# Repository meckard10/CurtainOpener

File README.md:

# CurtainOpener

*Continuation of 4820_AlarmClock project.*
*Melody Eckard, Elliot Phillips, Madeline Woehrman*

Melody Eckard

## Overview

Light-sensitive window curtain opener that will automatically open user's curtains to 
allow natural light to wake them up. UtilizesMSP430 to sense outside light and control 
the cutain opener.

## Folders

1. /schematics
	- contains pcb schematic files and 3D print designs

2. /code
	- contains MSP430 code files

3. /original\ material/
	- contains imported files from original project

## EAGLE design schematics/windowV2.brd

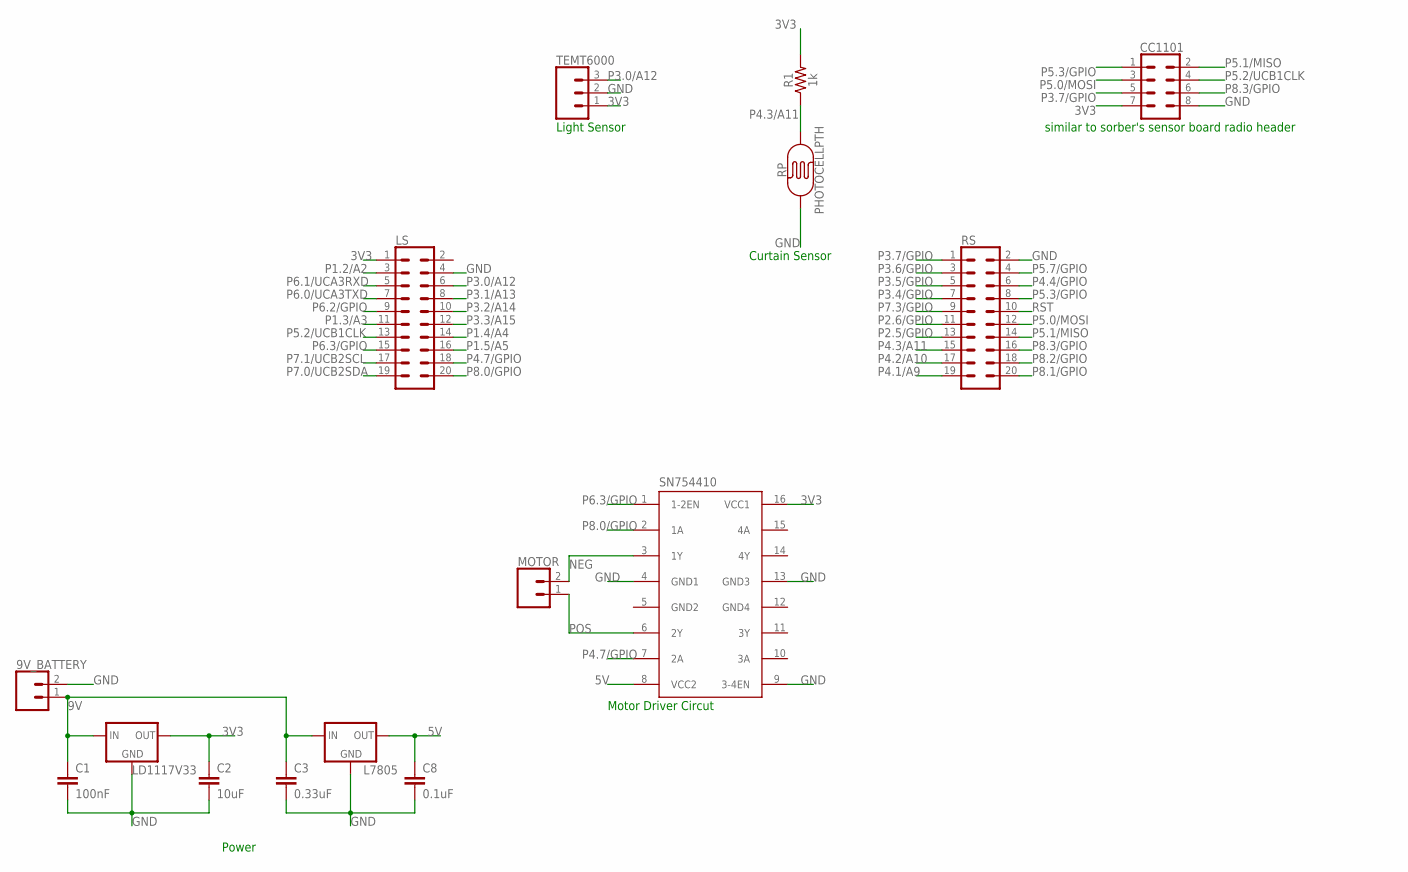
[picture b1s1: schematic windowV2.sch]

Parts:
9V_BATTERY: CONN_02; 1X02
C1: 100nF; C2.5-2
C2: 10uF; C2.5-2
C3: 0.33uF; C2.5-2
C8: 0.1uF; C2.5-2
CC1101: CONN_04X2; 2X4
L7805: V_REG_78XX-TO-220; TO-220-ALT
LD1117V33: V_REG_LD1117VXX; TO-220-ALT2
LS: CONN_10X2; 2X10
MOTOR: CONN_02; 1X02
R1: 1k; AXIAL-0.3
RP: PHOTOCELLPTH; PHOTOCELL
RS: CONN_10X2; 2X10
SN754410: L293D; DIL16
TEMT6000: 455-1750-1-ND; 1X03

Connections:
3V3: C2.1, CC1101.7, LD1117V33.OUT, LS.1, R1.P$2 (2), SN754410.16 (VCC1), TEMT6000.1
5V: C8.1, L7805.OUT, SN754410.8 (VCC2)
9V: 9V_BATTERY.1, C1.1, C3.1, L7805.IN, LD1117V33.IN
GND: 9V_BATTERY.2, C1.2, C2.2, C3.2, C8.2, CC1101.8, L7805.GND, LD1117V33.GND, LS.4, RP.1, RS.2, SN754410.4 (GND1), SN754410.9 (3-4EN), SN754410.13 (GND3), TEMT6000.2
GND2: SN754410.5 (GND2)
GND4: SN754410.12 (GND4)
NEG: MOTOR.2, SN754410.3 (1Y)
P1.2/A2: LS.3
P1.3/A3: LS.11
P1.4/A4: LS.14
P1.5/A5: LS.16
P2.5/GPIO: RS.13
P2.6/GPIO: RS.11
P3.0/A12: LS.6, TEMT6000.3
P3.1/A13: LS.8
P3.2/A14: LS.10
P3.3/A15: LS.12
P3.4/GPIO: RS.7
P3.5/GPIO: RS.5
P3.6/GPIO: RS.3
P3.7/GPIO: CC1101.5, RS.1
P4.1/A9: RS.19
P4.2/A10: RS.17
P4.3/A11: R1.P$1 (1), RP.2, RS.15
P4.4/GPIO: RS.6
P4.7/GPIO: LS.18, SN754410.7 (2A)
P5.0/MOSI: CC1101.3, RS.12
P5.1/MISO: CC1101.2, RS.14
P5.2/UCB1CLK: CC1101.4, LS.13
P5.3/GPIO: CC1101.1, RS.8
P5.7/GPIO: RS.4
P6.0/UCA3TXD: LS.7
P6.1/UCA3RXD: LS.5
P6.2/GPIO: LS.9
P6.3/GPIO: LS.15, SN754410.1 (1-2EN)
P7.0/UCB2SDA: LS.19
P7.1/UCB2SCL: LS.17
P7.3/GPIO: RS.9
P8.0/GPIO: LS.20, SN754410.2 (1A)
P8.1/GPIO: RS.20
P8.2/GPIO: RS.18
P8.3/GPIO: CC1101.6, RS.16
POS: MOTOR.1, SN754410.6 (2Y)
RST: RS.10

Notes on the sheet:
similar to sorber's sensor board radio header
Light Sensor
Motor Driver Circut
Power
Curtain Sensor

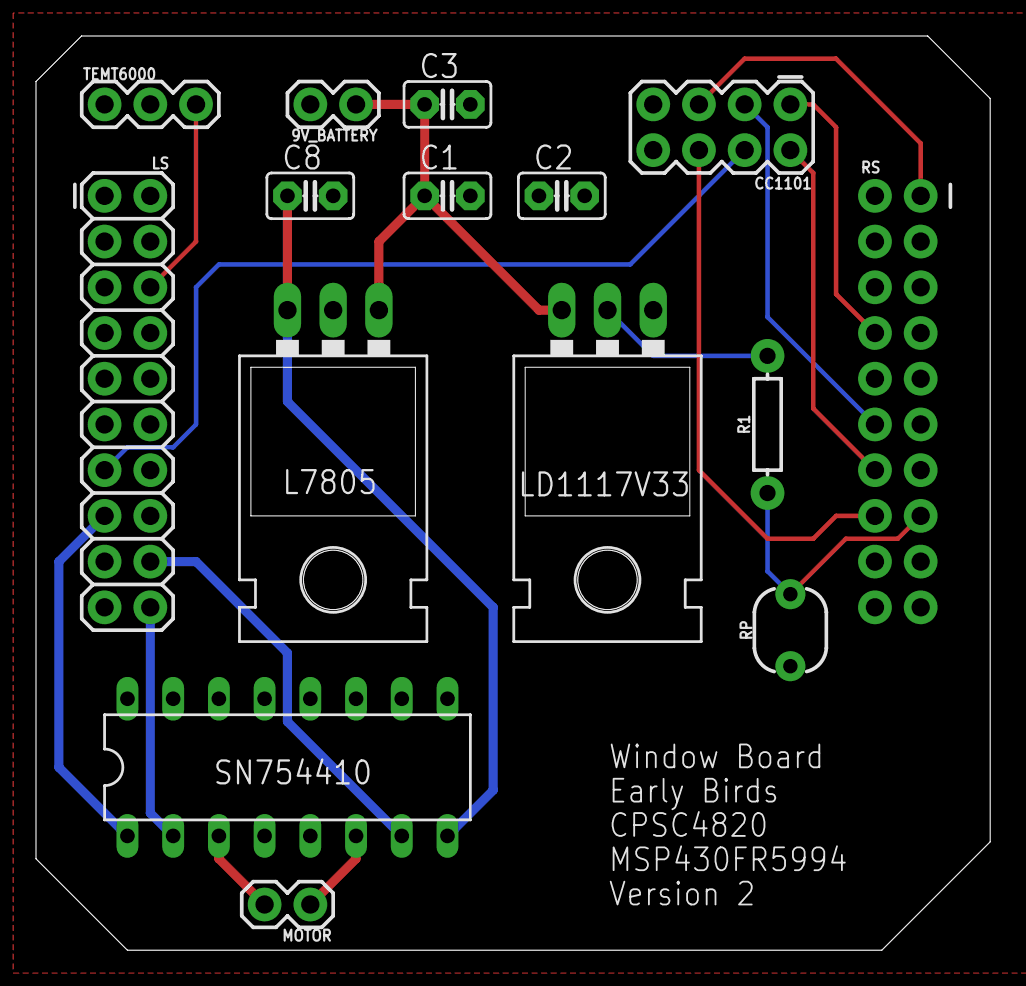
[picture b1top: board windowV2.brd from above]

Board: 2 copper layers, 53.0 x 50.8 mm, 15 parts (1 on the bottom side), 17 nets.

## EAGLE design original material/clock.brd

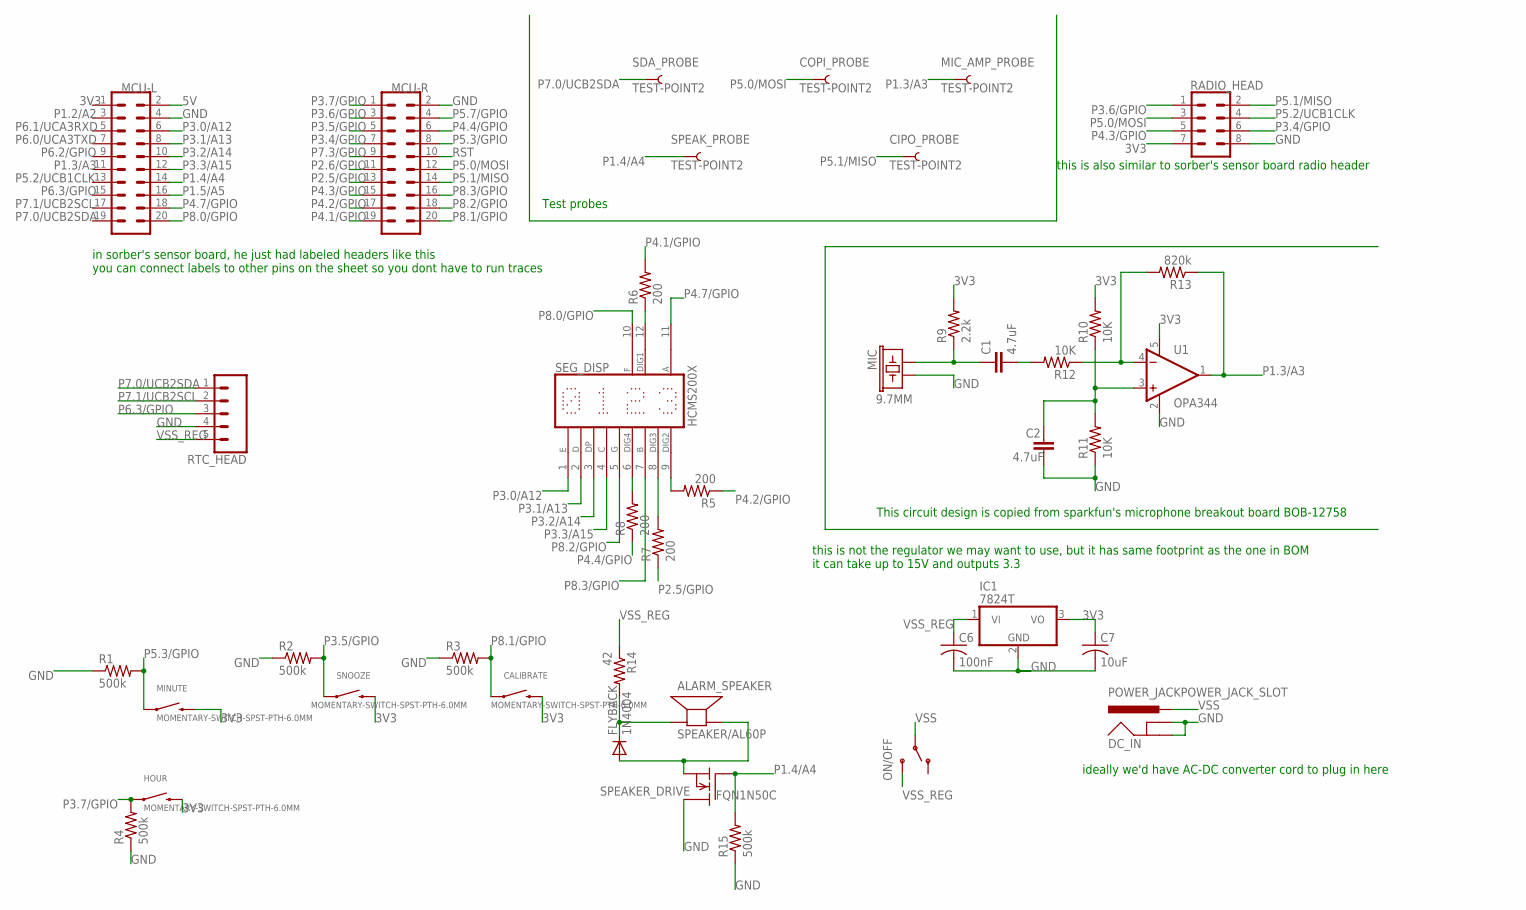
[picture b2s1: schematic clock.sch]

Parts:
ALARM_SPEAKER: SPEAKER/AL60P; AL60P
C1, C2: 4.7uF; 0603-CAP
C6: 100nF; C0805
C7: 10uF; C0805
CALIBRATE: MOMENTARY-SWITCH-SPST-PTH-6.0MM; TACTILE_SWITCH_PTH_6.0MM
CIPO_PROBE: TEST-POINT2; PAD.02X.02
COPI_PROBE: TEST-POINT2; PAD.02X.02
DC_IN: POWER_JACKPOWER_JACK_SLOT; POWER_JACK_PTH_SLOT
FLYBACK: 1N4004; DO41-10
HOUR: MOMENTARY-SWITCH-SPST-PTH-6.0MM; TACTILE_SWITCH_PTH_6.0MM
IC1: 7824T; TO220H
MCU-L: CONN_10X2; 2X10
MCU-R: CONN_10X2; 2X10
MIC: 9.7MM; MIC-9.7MM
MIC_AMP_PROBE: TEST-POINT2; PAD.02X.02
MINUTE: MOMENTARY-SWITCH-SPST-PTH-6.0MM; TACTILE_SWITCH_PTH_6.0MM
ON/OFF: SWITCH-SPDTSMD; SWITCH_SPDT_SMD
R1, R2, R3, R4: 500k; 0204/5
R5, R6, R7, R8: 200; 0204/7
R9: 2.2k; 0603-RES
R10, R11, R12: 10K; 0603-RES
R13: 820k; 0603-RES
R14: 42; 0204/7
R15: 500k; 0204/7
RADIO_HEAD: CONN_04X2; 2X4
RTC_HEAD: CONN_05LOCK; 1X05_LOCK
SDA_PROBE: TEST-POINT2; PAD.02X.02
SEG_DISP: HCMS200X
SNOOZE: MOMENTARY-SWITCH-SPST-PTH-6.0MM; TACTILE_SWITCH_PTH_6.0MM
SPEAKER_DRIVE: FQN1N50C; TO92
SPEAK_PROBE: TEST-POINT2; PAD.02X.02
U1: OPA344; SOT23-5

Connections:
3V3: C7.1, CALIBRATE.3 (2), HOUR.3 (2), IC1.3 (VO), MCU-L.1, MINUTE.3 (2), R9.2, R10.2, RADIO_HEAD.7, SNOOZE.3 (2), U1.5 (V+)
5V: MCU-L.2
GND: C2.2, C6.2, C7.2, DC_IN.GND, DC_IN.GNDBREAK, IC1.2 (GND), MCU-L.4, MCU-R.2, MIC.2, R1.1, R2.1, R3.1, R4.1, R11.1, R15.1, RADIO_HEAD.8, RTC_HEAD.4, SPEAKER_DRIVE.2 (D), U1.2 (V-)
MIC_TEST: C1.1, MIC.1, R9.1
unnamed: R8.2, SEG_DISP.6 (I-CO)
unnamed: R7.2, SEG_DISP.8 (VB)
unnamed: R5.2, SEG_DISP.9 (VDD)
unnamed: R6.1, SEG_DISP.12 (IN)
unnamed: R12.1, R13.2, U1.4 (-IN)
unnamed: C1.2, R12.2
unnamed: C2.1, R10.1, R11.2, U1.3 (+IN)
unnamed: ALARM_SPEAKER.2 (-), FLYBACK.A, SPEAKER_DRIVE.3 (S)
unnamed: ALARM_SPEAKER.1 (+), FLYBACK.C, R14.2
P1.2/A2: MCU-L.3
P1.3/A3: MCU-L.11, MIC_AMP_PROBE.1, R13.1, U1.1 (OUT)
P1.4/A4: MCU-L.14, R15.2, SPEAKER_DRIVE.1 (G), SPEAK_PROBE.1
P1.5/A5: MCU-L.16
P2.5/GPIO: MCU-R.13, R7.1
P2.6/GPIO: MCU-R.11
P3.0/A12: MCU-L.6, SEG_DISP.1 (COL1)
P3.1/A13: MCU-L.8, SEG_DISP.2 (COL2)
P3.2/A14: MCU-L.10, SEG_DISP.3 (COL3)
P3.3/A15: MCU-L.12, SEG_DISP.4 (COL4)
P3.4/GPIO: MCU-R.7, RADIO_HEAD.6
P3.5/GPIO: MCU-R.5, R2.2, SNOOZE.1
P3.6/GPIO: MCU-R.3, RADIO_HEAD.1
P3.7/GPIO: HOUR.1, MCU-R.1, R4.2
P4.1/GPIO: MCU-R.19, R6.2
P4.2/GPIO: MCU-R.17, R5.1
P4.3/GPIO: MCU-R.15, RADIO_HEAD.5
P4.4/GPIO: MCU-R.6, R8.1
P4.7/GPIO: MCU-L.18, SEG_DISP.11 (GND)
P5.0/MOSI: COPI_PROBE.1, MCU-R.12, RADIO_HEAD.3
P5.1/MISO: CIPO_PROBE.1, MCU-R.14, RADIO_HEAD.2
P5.2/UCB1CLK: MCU-L.13, RADIO_HEAD.4
P5.3/GPIO: MCU-R.8, MINUTE.1, R1.2
P5.7/GPIO: MCU-R.4
P6.0/UCA3TXD: MCU-L.7
P6.1/UCA3RXD: MCU-L.5
P6.2/GPIO: MCU-L.9
P6.3/GPIO: MCU-L.15, RTC_HEAD.3
P7.0/UCB2SDA: MCU-L.19, RTC_HEAD.1, SDA_PROBE.1
P7.1/UCB2SCL: MCU-L.17, RTC_HEAD.2
P7.3/GPIO: MCU-R.9
P8.0/GPIO: MCU-L.20, SEG_DISP.10 (CLK)
P8.1/GPIO: CALIBRATE.1, MCU-R.20, R3.2
P8.2/GPIO: MCU-R.18, SEG_DISP.5 (COL5)
P8.3/GPIO: MCU-R.16, SEG_DISP.7 (OUT)
RST: MCU-R.10
VSS: DC_IN.PWR, ON/OFF.2
VSS_REG: C6.1, IC1.1 (VI), ON/OFF.3 (S), R14.1, RTC_HEAD.5

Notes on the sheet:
in sorber's sensor board, he just had labeled headers like this you can connect labels to other pins on the sheet so you dont have to run traces
This circuit design is copied from sparkfun's microphone breakout board BOB-12758
this is also similar to sorber's sensor board radio header
this is not the regulator we may want to use, but it has same footprint as the one in BOM it can take up to 15V and outputs 3.3
ideally we'd have AC-DC converter cord to plug in here
Test probes

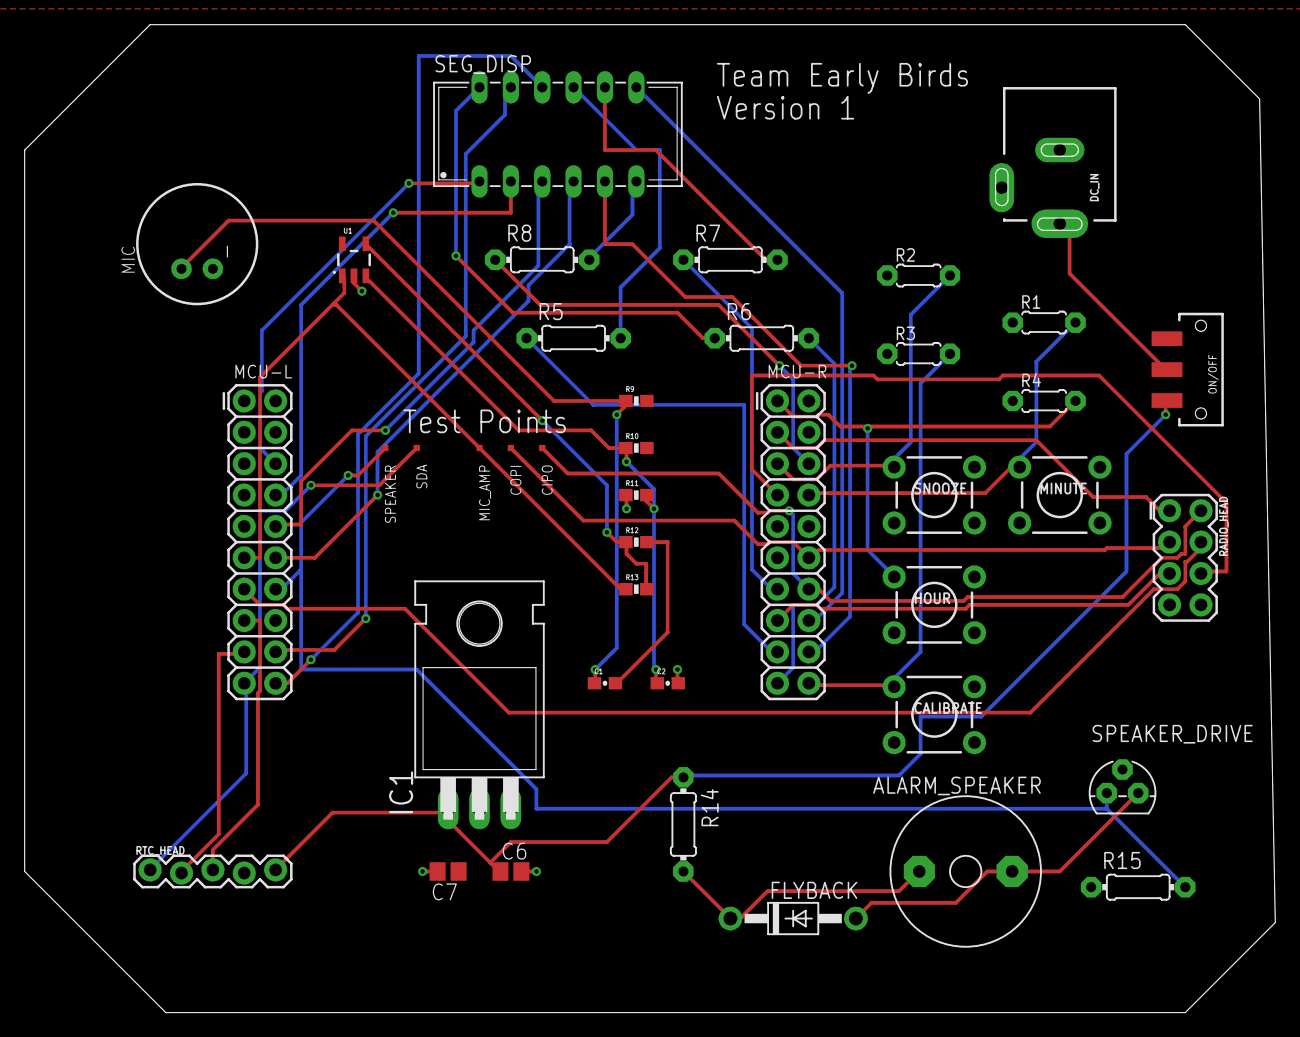
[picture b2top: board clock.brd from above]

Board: 2 copper layers, 101.3 x 80.0 mm, 41 parts (0 on the bottom side), 41 nets.

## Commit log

2024-08-29 initiated README file
2024-08-30 formated README and added folders
2024-08-30 added original materials
2025-04-04 added schematics

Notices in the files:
parts and their libraries:
SparkFun-Capacitors: Licensing: Creative Commons ShareAlike 4.0 International - https://creativecommons.org/licenses/by-sa/4.0
